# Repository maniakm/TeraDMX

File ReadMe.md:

TeraDMX
===========================
TeraDMX is fully isolated DMX LED DIMMER Shield for Arduino is designed to connect your project to professional large size DMX networks.
It can control high-current (9-24V lamps, relays, solenoids, motors, etc.) or low-current TTL (for servos and small LEDs) output.
This shield has been designed to restrain EMI and to eliminate ground loops specifically. Ideal for DMX projects without risking processor damages from high voltage peaks.

The shield is based on a ST485EBDR which has very good ESD protection properties, it allows you to connect up to 256 devices on a single bus!

All components have been carefully selected on their characteristics to ensure proper isolation and performance.

The following settings are configurable via the onboard jumpers:
- Receive data via RX or other pin via wire jumper
- PWM ch1 via 9 PIN or other pin via wire jumper
- PWM ch2 via 10 PIN or other pin via wire jumper
- PWM ch3 via 11 PIN or other pin via wire jumper
- Terminator 120 Ohm

The shield comes standard in a 5 pin XLR version, 3 pin versions is available as well. PCB is design to fit both of them.

Every board is tested before shipping to provide high quality service.

This DMX Shield is a high quality solution for reasonable costs that allows you to connect your Arduino driven artwork safely into DMX512 networks.

<p align="center">

<div align="center"><i>Foto: TeraDMX v.1.2</i></div>
</p>  

Features  
-------------------
+ <b>Open-source</b>  (Schematics, PCB layout, GERBER files and source code ale available for everyone for free)
+ <b>3 x 6A PWM LED outputs </b> 
+ 9-24V input
+ PCB designed for 3 or 5 XLR PIN sockets
+ Terminator 120 Ohm selected by jumper
+ Crossable control pins
+ <b>ESD protection</b> (ST485EBDR transceiver)<br>
 ± 15 kV (HBM)<br>
 ± 8 kV (IEC-1000-4-2 contact discharge)
+ <b>Opto isolation</b> (6N137SDM Transoptor)<br>
 Superior CMR - 10 kV/us
 + <b>Galvanic decoupling</b>  (DC/DC Converter)<br>
 Input / Output isolation 1000 VDC
+ LED Data indicator
 
Isolation  
-------------------
For a simple setup it is possible to connect the Driver chip directly to the Arduino pins but if you need a robust system, especially on a stage environment, you will have to add some more electronics to avoid electrical damage by defect equipment or accidental circumstances.

The electric potential of the DMX side of the implementation have to be isolated from the processor. There are 2 sort of chips that implement all you need:
- <b>A 5 volt to 5 volt DC/DC converter with galvanic decoupling.</b>
There are complete solutions in a single component available like AM1S-0505SZ that can be used to generate a 5V power supply that is galvanic isolated up to 1000V. So even if there is a high voltage attached to the DMX bus there is a chance of no or low damage.
- <b>High speed TTL compatible Optocoupler</b>
These chips use a LED and light sensitive transistor to isolate the DMX bus from the Arduino data pins. There are standard TTL compatible Optocouplers available like the 6N137.

Arduino Software  
-------------------
The Conceptinectics DMX Library for Arduino can be downloaded from the source forge website. https://sourceforge.net/projects/dmxlibraryforar/files/
<br>Sample code for this shield is provided below.

In case you have the shield configured to use the RX pin you have to disable the shield before you can upload your new sketch onto the Arduino board. This jumper allows you to disable the shield without disconnecting it from the Arduino board which saves time.

 ```c++
#include <Conceptinetics.h>

#define DMX_SLAVE_ADDRESS    1 //DMX address
#define DMX_SLAVE_CHANNELS   4 //DMX channels

// Configure a DMX slave controller
DMX_Slave dmx_slave ( DMX_SLAVE_CHANNELS );

//PIN configuration
const int StatusLed = 13;
const int PWM_R = 11;
const int PWM_G = 10;
const int PWM_B = 9;

unsigned long       lastFrameReceivedTime;
const unsigned long dmxTimeoutMillis = 10000UL;

// the setup routine runs once when you press reset:
void setup() {             

  // Enable DMX slave interface and start recording
  // DMX data
  dmx_slave.enable ();  
  
  // Set start address to 1, this is also the default setting
  // You can change this address at any time during the program
  dmx_slave.setStartAddress (DMX_SLAVE_ADDRESS);

  //
  // Register on frame complete event to determine signal timeout
  //
  dmx_slave.onReceiveComplete ( OnFrameReceiveComplete );
  
  // Set led pin as output pin
  pinMode ( PWM_R, OUTPUT );
  pinMode ( PWM_G, OUTPUT );
  pinMode ( PWM_B, OUTPUT );
  pinMode ( StatusLed, OUTPUT );
}

// the loop routine runs over and over again forever:
void loop() 
{
  
  float M = dmx_slave.getChannelValue (1) / 255.0f;
  int R = dmx_slave.getChannelValue (2) * M;
  int G = dmx_slave.getChannelValue (3) * M;
  int B = dmx_slave.getChannelValue (4) * M;

  analogWrite(PWM_R,R);
  analogWrite(PWM_G,G);
  analogWrite(PWM_B,B);

  if(millis() - lastFrameReceivedTime > 3000)
  {
    digitalWrite(StatusLed,HIGH);
    analogWrite(PWM_R,255);
    analogWrite(PWM_G,0);
    analogWrite(PWM_B,0);
  }
}

bool sta = false;
void OnFrameReceiveComplete (unsigned short channelsReceived)
{
  if ( channelsReceived == DMX_SLAVE_CHANNELS)
  {
    // All slave channels have been received
    //digitalWrite(StatusLed,LOW);    
  }
  else
  {
    // We have received a frame but not all channels we where 
    // waiting for, master might have transmitted less
    // channels
  }
  
  digitalWrite(StatusLed,sta);
  sta = !sta;
  // Update receive time to determine signal timeout
  lastFrameReceivedTime = millis ();
}
```

PC Software  
-------------------
You can use PC with DMX controller via USB (Enttec Open DMX) and special software (Q Light Controller).<br>
We provide configuration file for Q Light Controller as well.

Would you like to buy one?
-------------------
Great! Just send as an email.<br>
biuro@xirux.com<br>
150 PLN + 23% TAX<br>
(~38USD)

You can buy PCB as well (50 PLN)

-------------------
 
<br>

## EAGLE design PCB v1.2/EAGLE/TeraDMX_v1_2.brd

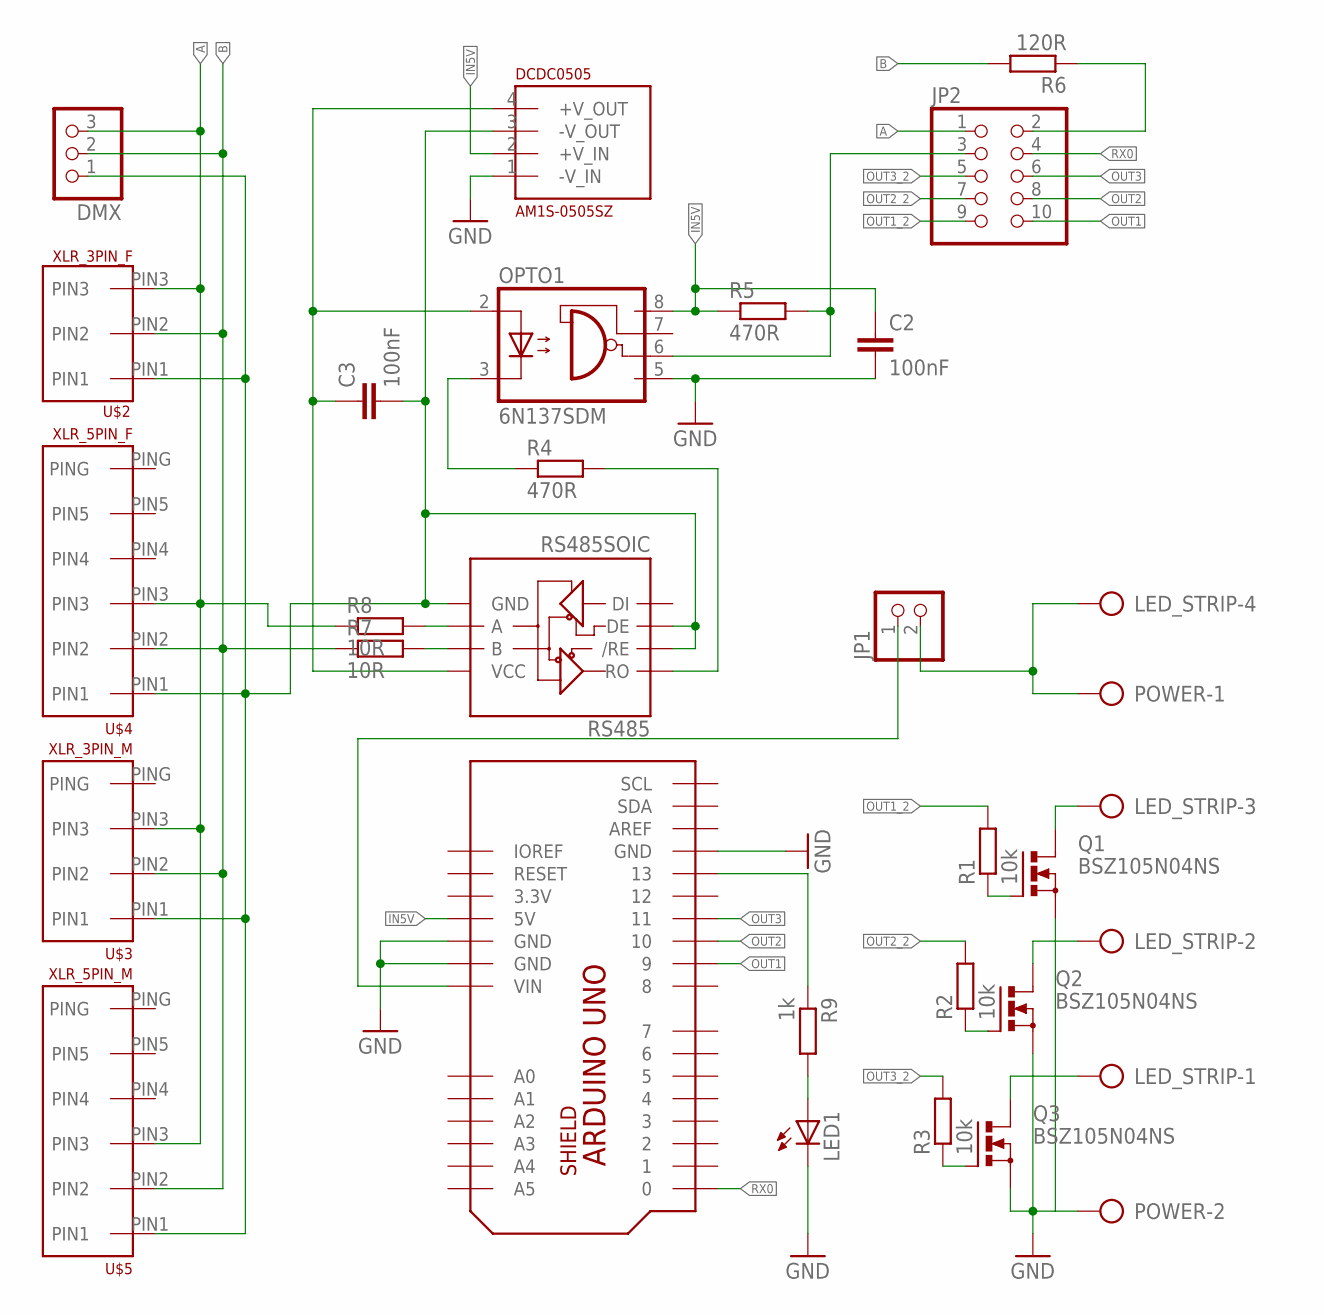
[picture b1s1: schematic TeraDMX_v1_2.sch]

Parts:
C2, C3: 100nF; C0805
DCDC0505: AM1S-0505SZ
DMX: PINHD-1X3; 1X03
JP1: PINHD-1X2; 1X02
JP2: PINHD-2X5; 2X05
LED1: LEDCHIP-LED0805; CHIP-LED0805
LED_STRIP: AK300/4
OPTO1: 6N137SDM
POWER: AK300/2
Q1, Q2, Q3: BSZ105N04NS; PG-TDSON-8
R1, R2, R3: 10k; M0805
R4: 470R; M0805
R5: 470R; R0805
R6: 120R; M0805
R7, R8: 10R; M0805
R9: 1k; M0805
RS485: RS485SOIC; SO08
U$2: XLR_3PIN_F
U$3: XLR_3PIN_M
U$4: XLR_5PIN_F
U$5: XLR_5PIN_M
U$6: ARDUINO_UNO_SHIELD

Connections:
3.3V: U$6.3.3V
A: DMX.3, JP2.1, R8.1, U$2.PIN3, U$3.PIN3, U$4.PIN3, U$5.PIN3
B: DMX.2, R6.2, R7.1, U$2.PIN2, U$3.PIN2, U$4.PIN2, U$5.PIN2
GND: C2.2, DCDC0505.1 (-V_IN), LED1.C, OPTO1.5 (GND), POWER.2, Q1.1 (S), Q1.2 (S), Q1.3 (S), Q2.1 (S), Q2.2 (S), Q2.3 (S), Q3.1 (S), Q3.2 (S), Q3.3 (S), U$6.GND1 (GND), U$6.GND2 (GND), U$6.GND3 (GND)
IN5V: C2.1, DCDC0505.2 (+V_IN), OPTO1.8 (VCC), R5.1, U$6.5V
unnamed: C3.2, DCDC0505.3 (-V_OUT), DMX.1, RS485.2 (/RE), RS485.3 (DE), RS485.5 (GND), U$2.PIN1, U$3.PIN1, U$4.PIN1, U$5.PIN1
unnamed: C3.1, DCDC0505.4 (+V_OUT), OPTO1.2 (A), RS485.8 (VCC)
unnamed: OPTO1.3 (C), R4.1
unnamed: LED_STRIP.1, Q3.5 (D), Q3.6 (D), Q3.7 (D), Q3.8 (D), Q3.TH (D)
unnamed: LED_STRIP.2, Q2.5 (D), Q2.6 (D), Q2.7 (D), Q2.8 (D), Q2.TH (D)
unnamed: LED_STRIP.3, Q1.5 (D), Q1.6 (D), Q1.7 (D), Q1.8 (D), Q1.TH (D)
unnamed: JP2.2, R6.1
unnamed: Q1.4 (G), R1.1
unnamed: Q2.4 (G), R2.1
unnamed: Q3.4 (G), R3.1
unnamed: R4.2, RS485.1 (RO)
unnamed: JP2.3, OPTO1.6 (VO), R5.2
unnamed: R7.2, RS485.7 (B)
unnamed: R8.2, RS485.6 (A)
unnamed: JP1.1, U$6.VIN
unnamed: R9.1, U$6.13
unnamed: LED1.A, R9.2
OUT1: JP2.10, U$6.9
OUT1_2: JP2.9, R1.2
OUT2: JP2.8, U$6.10
OUT2_2: JP2.7, R2.2
OUT3: JP2.6, U$6.11
OUT3_2: JP2.5, R3.2
PLUS: JP1.2, LED_STRIP.4, POWER.1
RX0: JP2.4, U$6.0

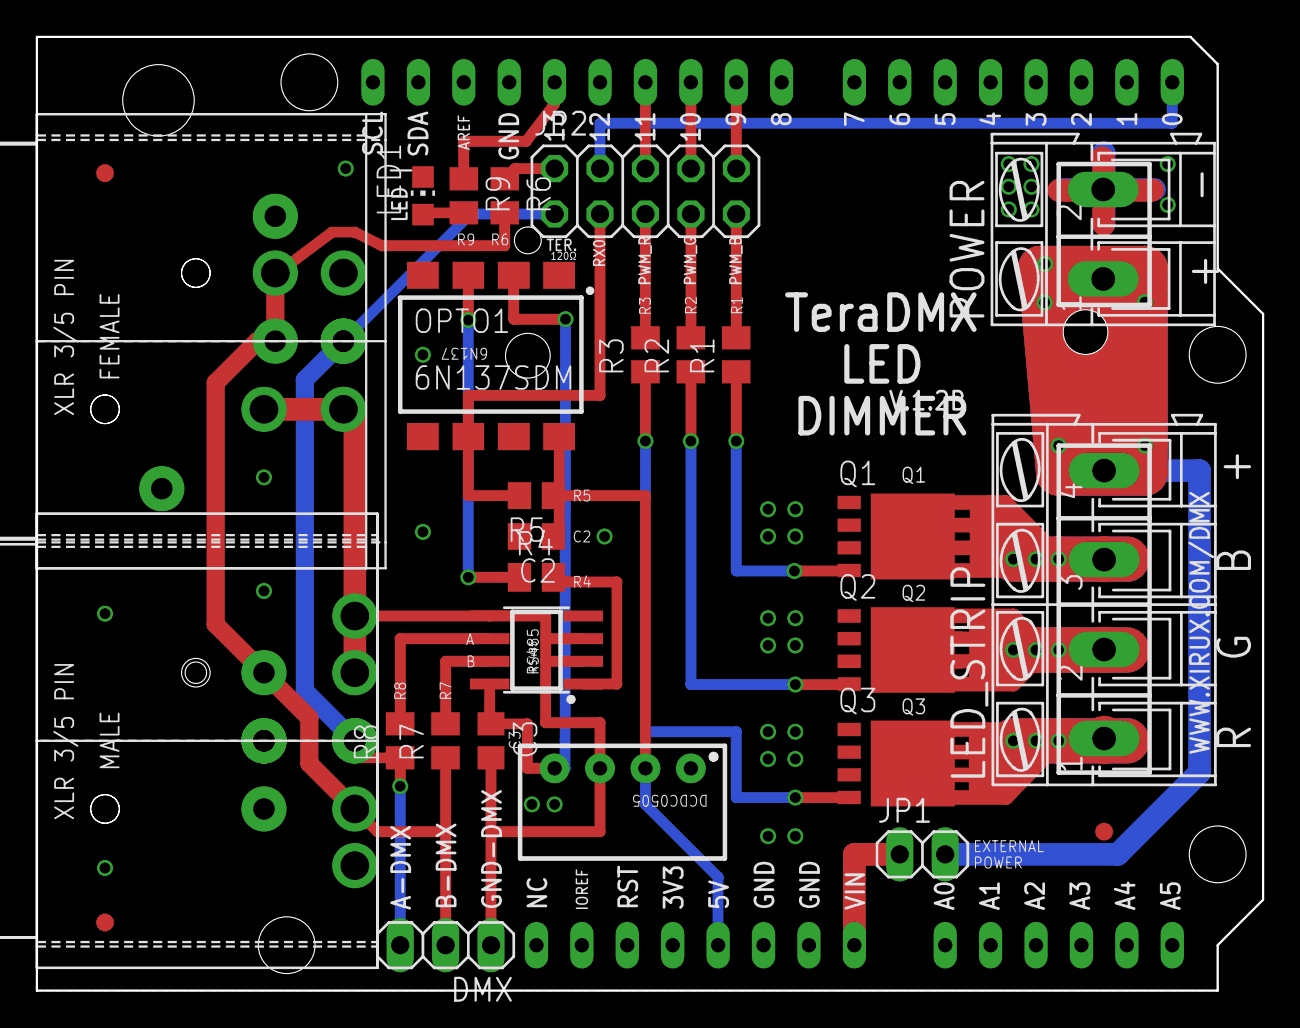
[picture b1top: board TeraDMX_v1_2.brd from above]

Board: 2 copper layers, 68.6 x 53.3 mm, 31 parts (0 on the bottom side), 29 nets.

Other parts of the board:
U$1, U$7, U$8: CIRCLE-1MM-3R

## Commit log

2016-05-24 :confetti_ball: Added .gitattributes
2016-05-27 First upload
    This is first files upload
2016-05-27 ReadMe fix
    Just ReadMe file update
2016-05-27 ReadMe file fix
2016-05-27 ReadMe file update
2016-05-27 InfoGFX update
2016-05-27 ReadMe update
2021-05-21 Update ReadMe.md
    Links update

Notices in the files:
parts and their libraries:
SparkFun-DigitalIC: Licensing: Creative Commons ShareAlike 4.0 International - https://creativecommons.org/licenses/by-sa/4.0
